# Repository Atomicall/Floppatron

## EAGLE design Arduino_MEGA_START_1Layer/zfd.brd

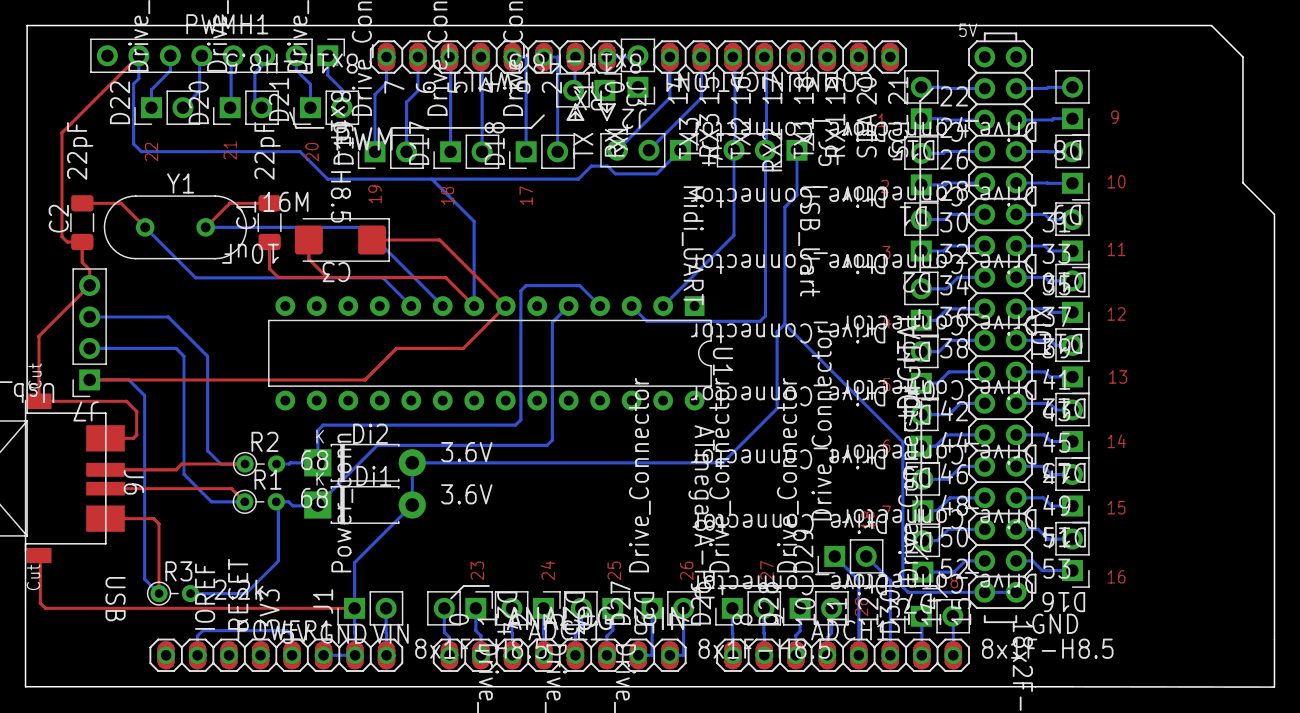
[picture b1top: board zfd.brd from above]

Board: 2 copper layers, 100.8 x 53.4 mm, 54 parts (0 on the bottom side), 76 nets.

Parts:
ADCH1: 8x1F-H8.5; P48
ADCL1: 8x1F-H8.5; P48
C1, C2: 22pF; P22
C3: 10uF; P1
COMMUNICATION1: 8x1F-H8.5; P48
D1, D2, D3, D4, D5, D6, D7, D8, D9, D10, D11, D12, D13, D14, D15, D16, D17, D18, D19, D20, D21, D22, D23, D24, D25, D26, D27, D28, D29, D30: Drive_Connector; P10
Di1, Di2: 3.6V; P8
J1: Power_conn; P10
J2: RX; P10
J3: TX; P10
J4: Midi_UART; P25
J5: USB_Uart; P25
J6: USB; P7
J7: Usb_ext; P0
POWER1: 8x1F-H8.5; P48
PWMH1: 8x1F-H8.5; P47
PWML1: 8x1F-H8.5; P48
R1, R2: 68; P4
R3: 2.2k; P4
U1: ATmega8A-PU; P3
XIO1: 18x2F-H8.5; P52
Y1: 16M; P2

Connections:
/+5v: POWER1.2, POWER1.5
/adc0: ADCL1.1, D24.2
/adc1: ADCL1.2, D24.1
/adc2: ADCL1.3, D23.2
/adc3: ADCL1.4, D23.1
/adc4: ADCL1.5, D25.2
/adc5: ADCL1.6, D25.1
/adc6: ADCL1.7, D27.1
/adc7: ADCL1.8, D27.2
/adc8: ADCH1.1, D26.1
/adc9: ADCH1.2, D26.2
/adc10: ADCH1.3, D28.1
/adc11: ADCH1.4, D28.2
/adc12: ADCH1.5, D29.1
/adc13: ADCH1.6, D29.2
/adc14: ADCH1.7, D30.1
/adc15: ADCH1.8, D30.2
/d+: Di2.1, R2.2, U1.4
/d-: Di1.1, R1.2, R3.2, U1.5
/dir1: D15.2, XIO1.3
/dir2: D1.2, XIO1.7
/dir3: D2.2, XIO1.11
/dir4: D3.2, XIO1.15
/dir5: D4.2, XIO1.19
/dir6: D5.2, XIO1.23
/dir7: D6.2, XIO1.27
/dir8: D7.2, XIO1.31
/dir9: D8.2, XIO1.4
/dir10: D9.2, XIO1.8
/dir11: D10.2, XIO1.12
/dir12: D11.2, XIO1.16
/dir13: D12.2, XIO1.20
/dir14: D13.2, XIO1.24
/dir15: D14.2, XIO1.28
/dir16: D16.2, XIO1.32
/dir17: D18.2, PWML1.3
/dir18: D17.2, PWML1.5
/dir19: D19.2, PWML1.7
/dir20: D21.2, PWMH1.1
/dir21: D20.2, PWMH1.3
/dir22: D22.2, PWMH1.5
/p24: D15.1, XIO1.5
/p25: D8.1, XIO1.6
/p28: D1.1, XIO1.9
/p29: D9.1, XIO1.10
/p32: D2.1, XIO1.13
/p33: D10.1, XIO1.14
/p36: D3.1, XIO1.17
/p37: D11.1, XIO1.18
/p40: D4.1, XIO1.21
/p41: D12.1, XIO1.22
/p44: D5.1, XIO1.25
/p45: D13.1, XIO1.26
/p48: D6.1, XIO1.29
/p49: D14.1, XIO1.30
/p52: D7.1, XIO1.33
/p53: D16.1, XIO1.34
/pb5: D20.1, PWMH1.4
/pb7: D22.1, PWMH1.6
/pe0: J2.2, PWML1.1
/pe1: J3.2, PWML1.2
/pe3: D17.1, PWML1.6
/pe5: D18.1, PWML1.4
/ph4: D19.1, PWML1.8
/ph6: D21.1, PWMH1.2
/rxd2: COMMUNICATION1.5, J5.2, U1.3
/rxd3: COMMUNICATION1.7, J4.2
/txd2: COMMUNICATION1.6, J5.3, U1.2
/txd3: COMMUNICATION1.8, J4.3
/u_vcc: C3.1, J6.1, J7.1, R3.1, U1.7
/vin: J1.2, POWER1.8
gnd: C1.1, C2.1, C3.2, Di1.2, Di2.2, J1.1, J4.1, J5.1, J6.4, J6.4@, J6.4@_1, J7.4, POWER1.6, POWER1.7, PWMH1.7, U1.8, XIO1.35, XIO1.36
net-(c1-pad2): C1.2, U1.9, Y1.2
net-(c2-pad2): C2.2, U1.10, Y1.1
net-(j6-pad2): J6.2, J7.2, R1.1
net-(j6-pad3): J6.3, J7.3, R2.1
